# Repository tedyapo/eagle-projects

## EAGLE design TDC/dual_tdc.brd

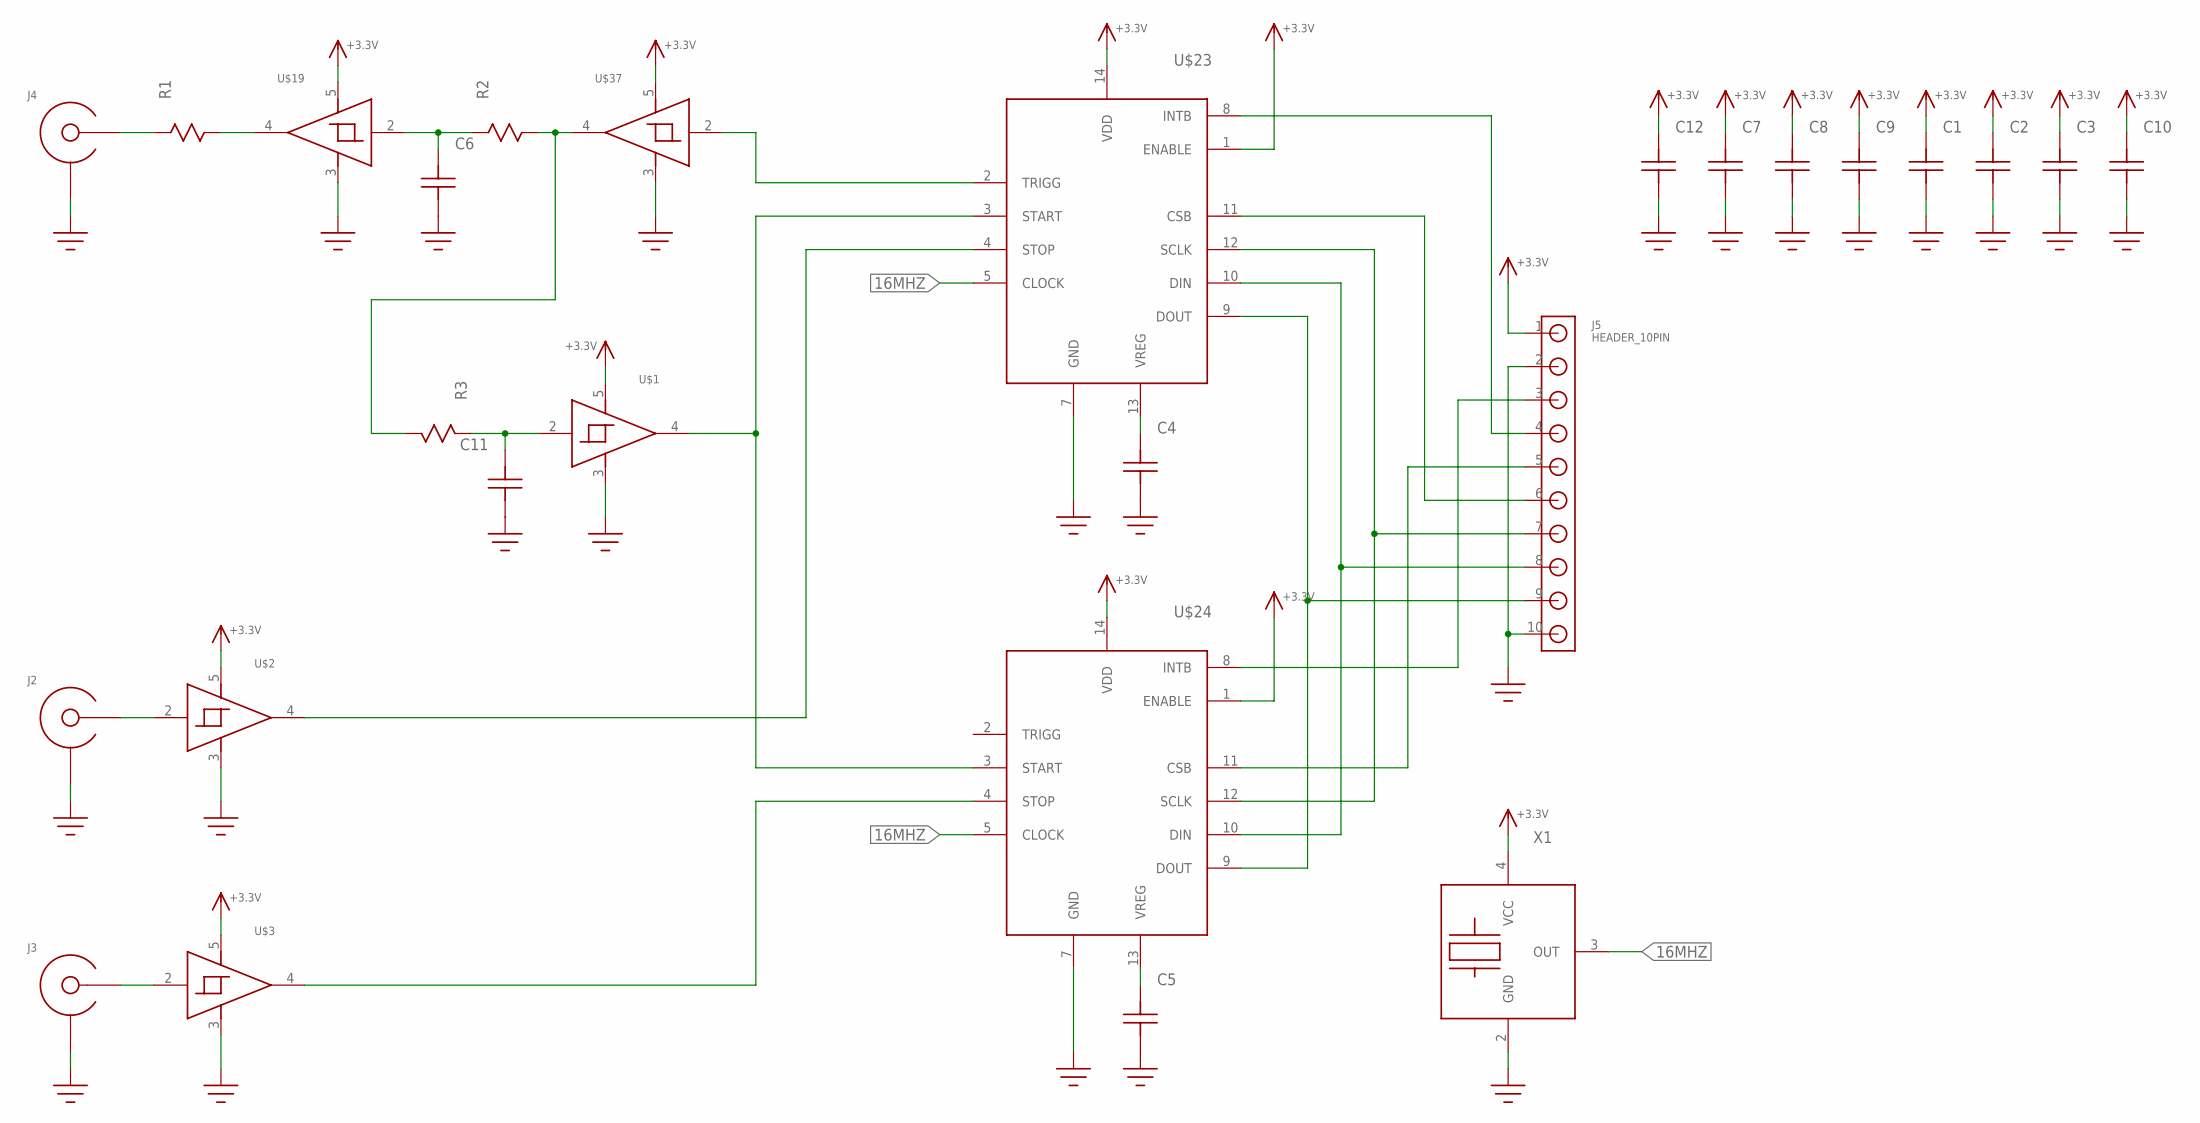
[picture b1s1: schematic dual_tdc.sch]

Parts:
C1, C2, C3, C6, C7, C8, C9, C10, C11, C12: C0603
C4, C5: C0805; 0805
J2, J3, J4: EDGE_LAUNCH_JACK; EDGE_LAUNCH_RF_CON
J5: HEADER_10PIN
R1: R0805
R2, R3: R0603
U$1, U$2, U$3, U$19, U$37: 74LVC1G17; SOT23-5
U$23, U$24: TDC7200TSSOP; TSSOP14
X1: XTAL_OSC; XTAL_3.2X5

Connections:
16MHZ: U$23.5 (CLOCK), U$24.5 (CLOCK), X1.3 (OUT)
+3.3V: C1.P$2, C2.P$2, C3.P$2, C7.P$2, C8.P$2, C9.P$2, C10.P$2, C12.P$2, J5.1, U$1.5 (VCC), U$2.5 (VCC), U$3.5 (VCC), U$19.5 (VCC), U$23.1 (ENABLE), U$23.14 (VDD), U$24.1 (ENABLE), U$24.14 (VDD), U$37.5 (VCC), X1.4 (VCC)
CH1: J2.CENTER, U$2.2 (IN)
CH2: J3.CENTER, U$3.2 (IN)
CSB2: J5.5, U$24.11 (CSB)
DIN: J5.8, U$23.10 (DIN), U$24.10 (DIN)
DOUT: J5.9, U$23.9 (DOUT), U$24.9 (DOUT)
GND: C1.P$1, C2.P$1, C3.P$1, C4.P$1, C5.P$1, C6.P$1, C7.P$1, C8.P$1, C9.P$1, C10.P$1, C11.P$1, C12.P$1, J2.GND@1 (SHIELD), J2.GND@2 (SHIELD), J2.GND@3 (SHIELD), J2.GND@4 (SHIELD), J2.GND@5 (SHIELD), J2.GND@6 (SHIELD), J2.GND@7 (SHIELD), J2.GND@8 (SHIELD), J2.GND@9 (SHIELD), J2.GND@10 (SHIELD), J2.GND@11 (SHIELD), J2.GND@12 (SHIELD), J2.SHIELD@1 (SHIELD), J2.SHIELD@2 (SHIELD), J3.GND@1 (SHIELD), J3.GND@2 (SHIELD), J3.GND@3 (SHIELD), J3.GND@4 (SHIELD), J3.GND@5 (SHIELD), J3.GND@6 (SHIELD), J3.GND@7 (SHIELD), J3.GND@8 (SHIELD), J3.GND@9 (SHIELD), J3.GND@10 (SHIELD), J3.GND@11 (SHIELD), J3.GND@12 (SHIELD), J3.SHIELD@1 (SHIELD), J3.SHIELD@2 (SHIELD), J4.GND@1 (SHIELD), J4.GND@2 (SHIELD), J4.GND@3 (SHIELD), J4.GND@4 (SHIELD), J4.GND@5 (SHIELD), J4.GND@6 (SHIELD), J4.GND@7 (SHIELD), J4.GND@8 (SHIELD), J4.GND@9 (SHIELD), J4.GND@10 (SHIELD), J4.GND@11 (SHIELD), J4.GND@12 (SHIELD), J4.SHIELD@1 (SHIELD), J4.SHIELD@2 (SHIELD), J5.2, J5.10, U$1.3 (GND), U$2.3 (GND), U$3.3 (GND), U$19.3 (GND), U$23.7 (GND), U$24.7 (GND), U$37.3 (GND), X1.2 (GND)
INTB1: J5.4, U$23.8 (INTB)
INTB2: J5.3, U$24.8 (INTB)
unnamed: U$23.2 (TRIGG), U$37.2 (IN)
unnamed: J5.6, U$23.11 (CSB)
unnamed: J4.CENTER, R1.P$1
unnamed: R1.P$2, U$19.4 (OUT)
unnamed: C6.P$2, R2.P$1, U$19.2 (IN)
unnamed: C4.P$2, U$23.13 (VREG)
unnamed: C5.P$2, U$24.13 (VREG)
unnamed: U$1.4 (OUT), U$23.3 (START), U$24.3 (START)
unnamed: C11.P$2, R3.P$1, U$1.2 (IN)
unnamed: U$2.4 (OUT), U$23.4 (STOP)
unnamed: U$3.4 (OUT), U$24.4 (STOP)
unnamed: R2.P$2, R3.P$2, U$37.4 (OUT)
SCLK: J5.7, U$23.12 (SCLK), U$24.12 (SCLK)

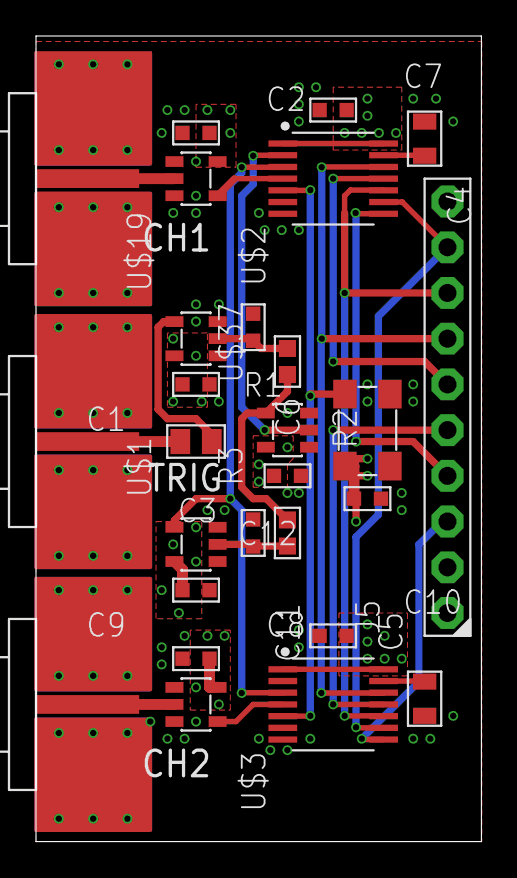
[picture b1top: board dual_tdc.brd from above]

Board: 4 copper layers, 24.7 x 44.8 mm, 27 parts (0 on the bottom side), 23 nets.

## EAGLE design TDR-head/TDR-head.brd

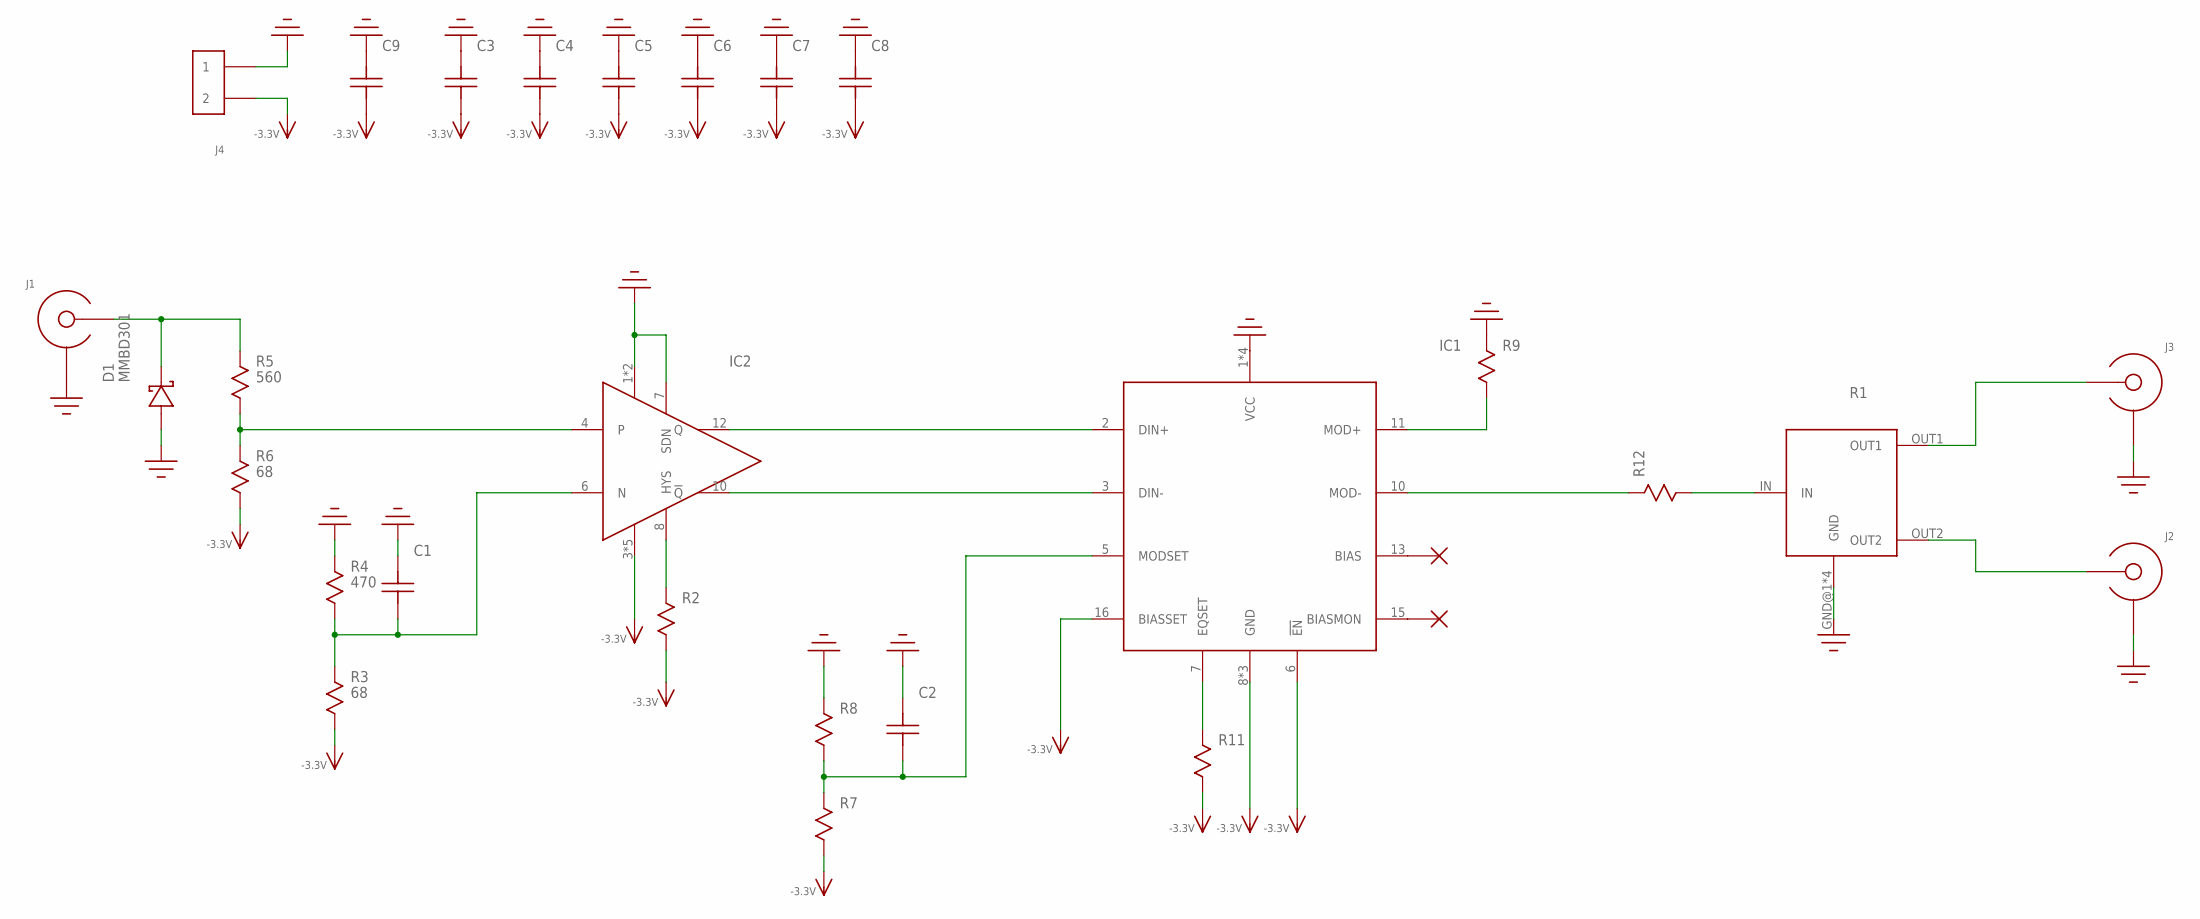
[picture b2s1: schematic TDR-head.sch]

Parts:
C1, C2: C0603
C3, C4, C5, C6, C7, C8: C; C0402
C9: C1206; 1206
D1: MMBD301; SOT-23
IC1: SY88022AL; TQFN16-EP
IC2: ADCMP607; QFN12-3X3
J1, J2, J3: SMA-EDGE-LAUNCH4020N5; SMA_EDGE_LAUNCH_4L_4020_N5
J4: HEADER_2PIN
R1: PS2012G-SPLITTER
R2, R7, R8, R11: R0603
R3, R6: 68; R0603
R4: 470; R0603
R5: 560; R0603
R9, R12: R0402; 0402

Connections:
-3.3V: C3.1, C4.1, C5.1, C6.1, C7.1, C8.1, C9.P$1, IC1.6 (!EN!), IC1.8 (GND), IC1.14 (GND), IC1.16 (BIASSET), IC1.EP (GND), IC2.3 (VEE), IC2.5 (VEE), IC2.9 (VEE), IC2.11 (VEE), IC2.EP (VEE), J4.2, R2.P$2, R3.P$2, R6.P$2, R7.P$2, R11.P$2
GND: C1.P$2, C2.P$2, C3.2, C4.2, C5.2, C6.2, C7.2, C8.2, C9.P$2, D1.1 (ANODE), IC1.1 (VCC), IC1.4 (VCC), IC1.9 (VCC), IC1.12 (VCC), IC2.1 (VCC), IC2.2 (VCC), IC2.7 (SDN), J1.BOTTOM_GND (SHIELD), J1.GND@1 (SHIELD), J1.GND@2 (SHIELD), J1.GND@3 (SHIELD), J1.GND@4 (SHIELD), J1.GND@5 (SHIELD), J1.GND@6 (SHIELD), J1.GND@7 (SHIELD), J1.GND@8 (SHIELD), J1.GND@9 (SHIELD), J1.GND@10 (SHIELD), J1.GND@14 (SHIELD), J1.GND@15 (SHIELD), J1.GND@16 (SHIELD), J1.GND@17 (SHIELD), J1.GND_PAD1 (SHIELD), J1.GND_PAD2 (SHIELD), J1.P$1 (SHIELD), J1.P$2 (SHIELD), J1.P$3 (SHIELD), J1.P$4 (SHIELD), J1.P$5 (SHIELD), J2.BOTTOM_GND (SHIELD), J2.GND@1 (SHIELD), J2.GND@2 (SHIELD), J2.GND@3 (SHIELD), J2.GND@4 (SHIELD), J2.GND@5 (SHIELD), J2.GND@6 (SHIELD), J2.GND@7 (SHIELD), J2.GND@8 (SHIELD), J2.GND@9 (SHIELD), J2.GND@10 (SHIELD), J2.GND@14 (SHIELD), J2.GND@15 (SHIELD), J2.GND@16 (SHIELD), J2.GND@17 (SHIELD), J2.GND_PAD1 (SHIELD), J2.GND_PAD2 (SHIELD), J2.P$1 (SHIELD), J2.P$2 (SHIELD), J2.P$3 (SHIELD), J2.P$4 (SHIELD), J2.P$5 (SHIELD), J3.BOTTOM_GND (SHIELD), J3.GND@1 (SHIELD), J3.GND@2 (SHIELD), J3.GND@3 (SHIELD), J3.GND@4 (SHIELD), J3.GND@5 (SHIELD), J3.GND@6 (SHIELD), J3.GND@7 (SHIELD), J3.GND@8 (SHIELD), J3.GND@9 (SHIELD), J3.GND@10 (SHIELD), J3.GND@14 (SHIELD), J3.GND@15 (SHIELD), J3.GND@16 (SHIELD), J3.GND@17 (SHIELD), J3.GND_PAD1 (SHIELD), J3.GND_PAD2 (SHIELD), J3.P$1 (SHIELD), J3.P$2 (SHIELD), J3.P$3 (SHIELD), J3.P$4 (SHIELD), J3.P$5 (SHIELD), J4.1, R1.GND@1 (GND), R1.GND@2 (GND), R1.GND@3 (GND), R1.GND@4 (GND), R4.P$1, R8.P$1, R9.1
unnamed: J2.CENTER@1 (CENTER), J2.CENTER@2 (CENTER), R1.OUT2
unnamed: J3.CENTER@1 (CENTER), J3.CENTER@2 (CENTER), R1.OUT1
unnamed: IC1.2 (DIN+), IC2.12 (Q)
unnamed: IC1.3 (DIN-), IC2.10 (!Q!)
unnamed: IC2.8 (HYS), R2.P$1
unnamed: C1.P$1, IC2.6 (N), R3.P$1, R4.P$2
unnamed: D1.3 (CATHODE), J1.CENTER@1 (CENTER), J1.CENTER@2 (CENTER), R5.P$1
unnamed: IC2.4, R5.P$2, R6.P$1
unnamed: C2.P$1, IC1.5 (MODSET), R7.P$1, R8.P$2
unnamed: R1.IN, R12.2
unnamed: IC1.11 (MOD+), R9.2
unnamed: IC1.7 (EQSET), R11.P$1
unnamed: IC1.10 (MOD-), R12.1

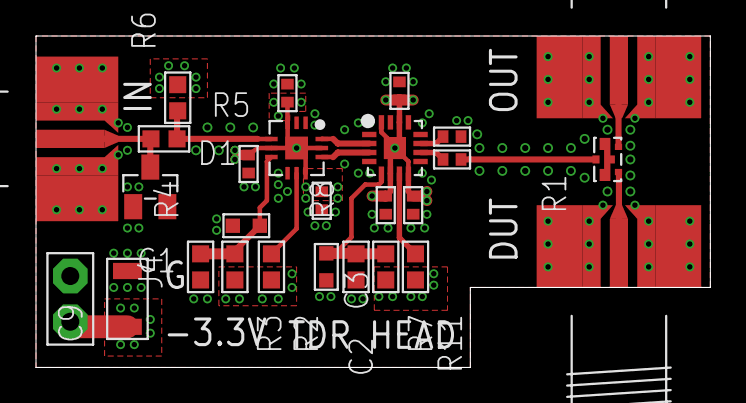
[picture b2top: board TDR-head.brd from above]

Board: 4 copper layers, 37.5 x 18.4 mm, 27 parts (0 on the bottom side), 15 nets.

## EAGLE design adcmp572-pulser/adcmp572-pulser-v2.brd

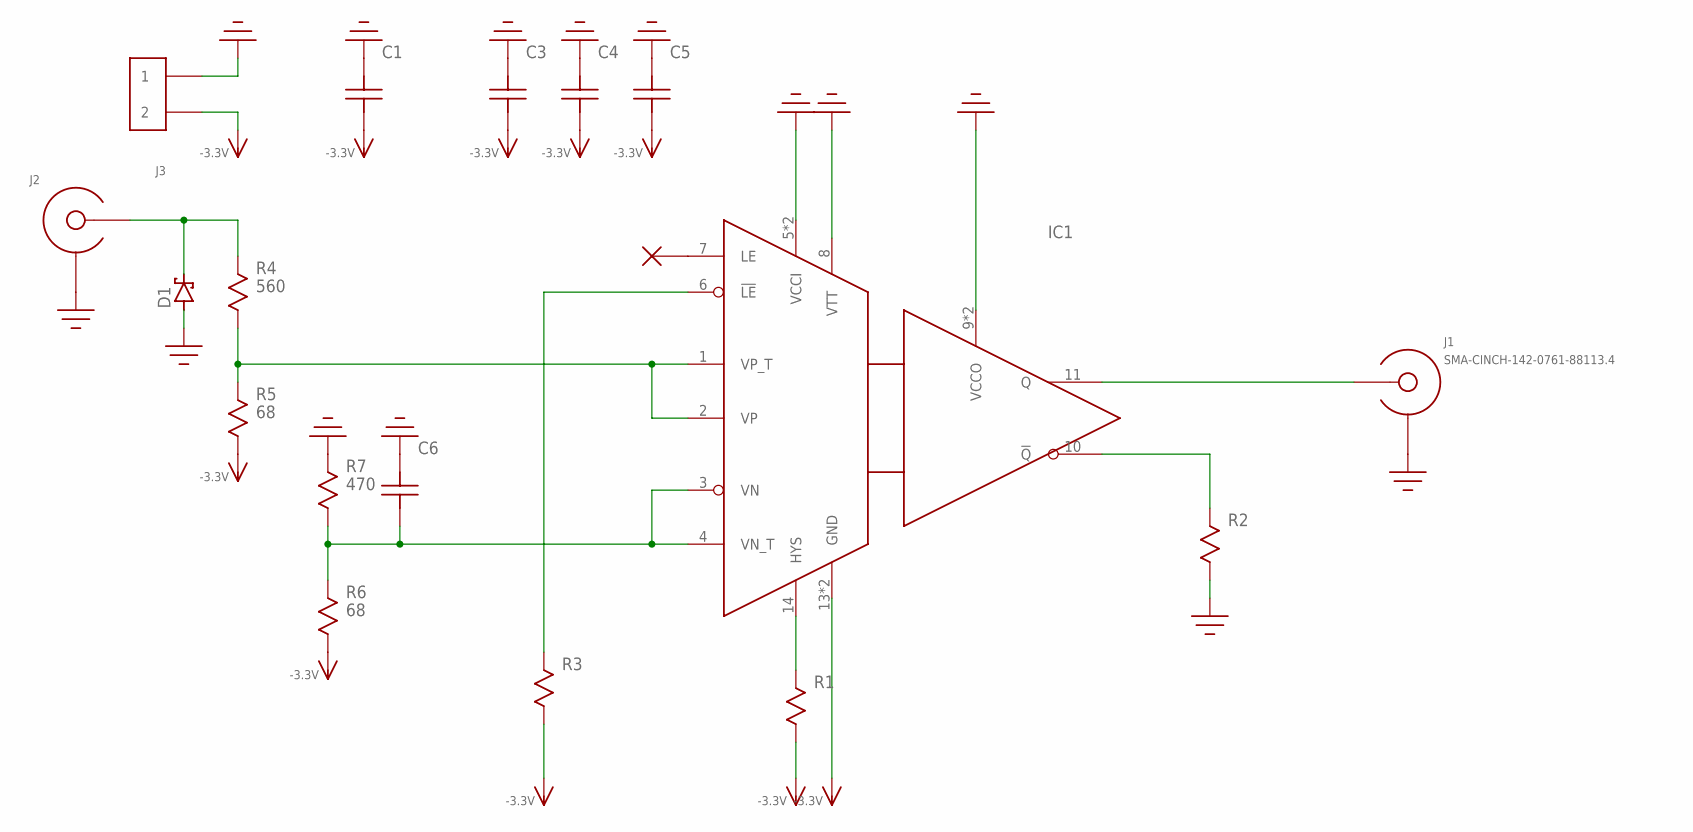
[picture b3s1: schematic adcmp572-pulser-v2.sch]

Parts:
C1: C1206; 1206
C3, C6: C0603
C4, C5: C; C0402
D1: SCHOTTKY; SOT-23
IC1: ADCMP572; TQFN16-EP
J1: SMA-CINCH-142-0761-88113.4; SMA-CINCH-142-0761-881-13.4
J2: SMA-EDGE-LAUNCH4L-4020-TAPER-FIXED; SMA_EDGE_LAUNCH_4L_4020_TAPER_FIXED
J3: HEADER_2PIN
R1, R3: R0603
R2: R0402; 0402
R4: 560; R0603
R5, R6: 68; R0603
R7: 470; R0603

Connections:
-3.3V: C1.P$1, C3.P$1, C4.1, C5.1, IC1.13 (GND), IC1.15 (GND), J3.2, R1.P$2, R3.P$2, R5.P$2, R6.P$2
GND: C1.P$2, C3.P$2, C4.2, C5.2, C6.P$2, D1.1 (A), IC1.5 (VCCI), IC1.8 (VTT), IC1.9 (VCCO), IC1.12 (VCCO), IC1.16 (VCCI), J1.GND@1 (SHIELD), J1.GND@2 (SHIELD), J1.GND@3 (SHIELD), J1.HOLE@1 (SHIELD), J1.HOLE@2 (SHIELD), J1.HOLE@3 (SHIELD), J1.HOLE@4 (SHIELD), J1.VIA@1 (SHIELD), J1.VIA@2 (SHIELD), J1.VIA@3 (SHIELD), J1.VIA@4 (SHIELD), J1.VIA@5 (SHIELD), J1.VIA@6 (SHIELD), J2.BOTTOM_GND (SHIELD), J2.GND@1 (SHIELD), J2.GND@2 (SHIELD), J2.GND@3 (SHIELD), J2.GND@4 (SHIELD), J2.GND@5 (SHIELD), J2.GND@6 (SHIELD), J2.GND@7 (SHIELD), J2.GND@8 (SHIELD), J2.GND@14 (SHIELD), J2.GND@15 (SHIELD), J2.GND@16 (SHIELD), J2.GND@17 (SHIELD), J2.GND_PAD1 (SHIELD), J2.GND_PAD2 (SHIELD), J2.P$1 (SHIELD), J2.P$2 (SHIELD), J3.1, R2.2, R7.P$1
unnamed: IC1.14 (HYS), R1.P$1
unnamed: IC1.10 (!Q!), R2.1
unnamed: C6.P$1, IC1.3 (VN), IC1.4 (VN_T), R6.P$1, R7.P$2
unnamed: IC1.1 (VP_T), IC1.2 (VP), R4.P$2, R5.P$1
unnamed: IC1.6 (!LE!), R3.P$1
unnamed: IC1.11 (Q), J1.CENTER
unnamed: D1.3 (C), J2.CENTER@1 (CENTER), J2.P$3 (CENTER), R4.P$1

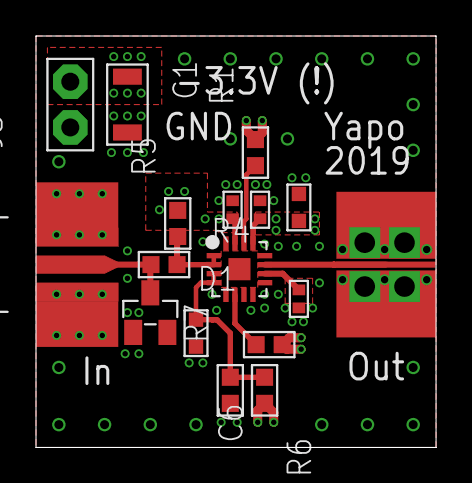
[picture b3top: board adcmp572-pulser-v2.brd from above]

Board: 4 copper layers, 22.2 x 22.9 mm, 17 parts (0 on the bottom side), 9 nets.

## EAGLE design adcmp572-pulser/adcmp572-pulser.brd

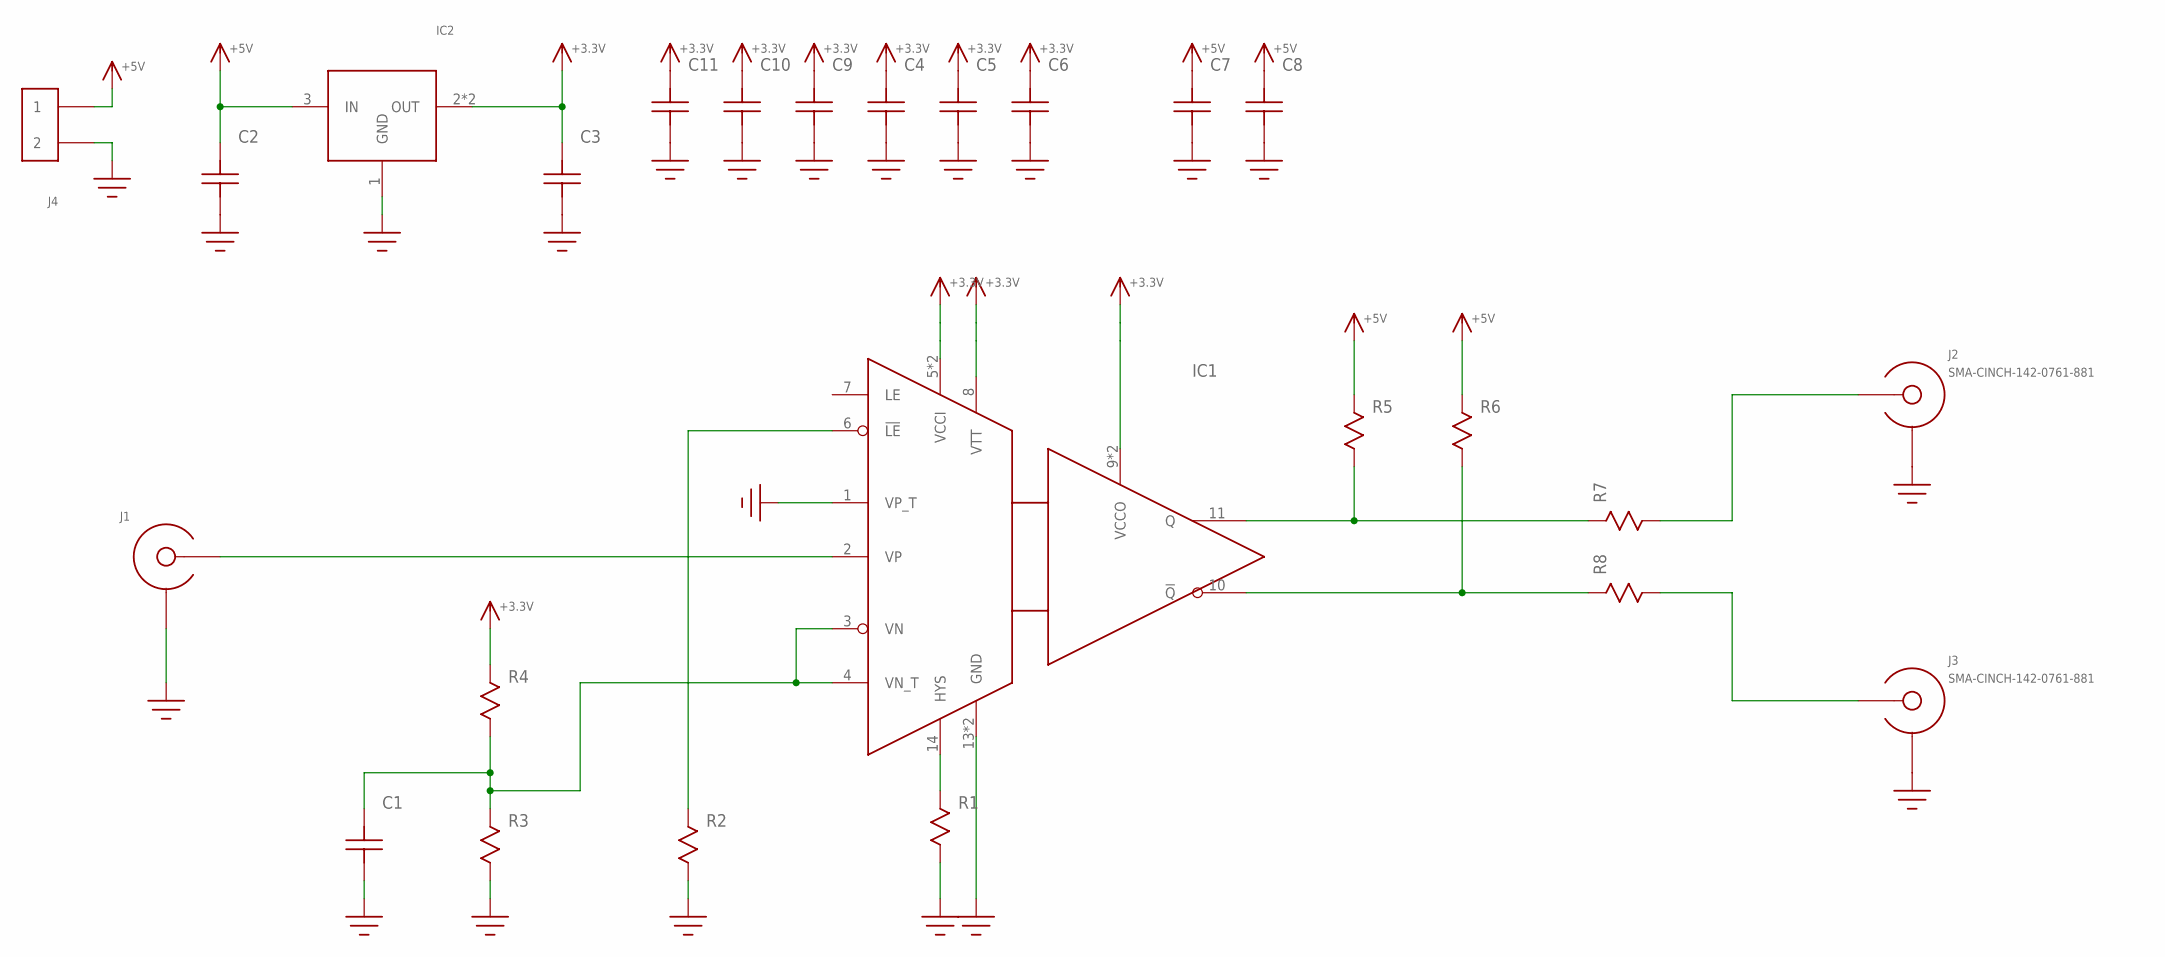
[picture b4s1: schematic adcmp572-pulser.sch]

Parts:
C1: C0603
C2, C3: C1206; 1206
C4, C5, C6, C7, C8, C9: C; C0402
C10, C11: C0201; 0201
IC1: ADCMP572; TQFN16-EP
IC2: AZ1117E; SOT-223
J1: SMA-EDGE-LAUNCH4L-4020-TAPER-FIXED; SMA_EDGE_LAUNCH_4L_4020_TAPER_FIXED
J2, J3: SMA-CINCH-142-0761-881
J4: HEADER_2PIN
R1, R2, R3, R4: R0603
R5, R6, R7, R8: R0402; 0402

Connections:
+3.3V: C3.P$2, C4.2, C5.2, C6.2, C9.2, C10.P$2, C11.P$2, IC1.5 (VCCI), IC1.8 (VTT), IC1.9 (VCCO), IC1.12 (VCCO), IC1.16 (VCCI), IC2.2 (OUT), IC2.4 (OUT), R4.P$1
+5V: C2.P$2, C7.2, C8.2, IC2.3 (IN), J4.1, R5.1, R6.1
GND: C1.P$1, C2.P$1, C3.P$1, C4.1, C5.1, C6.1, C7.1, C8.1, C9.1, C10.P$1, C11.P$1, IC1.1 (VP_T), IC1.13 (GND), IC1.15 (GND), IC2.1 (GND), J1.BOTTOM_GND (SHIELD), J1.GND@1 (SHIELD), J1.GND@2 (SHIELD), J1.GND@3 (SHIELD), J1.GND@4 (SHIELD), J1.GND@5 (SHIELD), J1.GND@6 (SHIELD), J1.GND@7 (SHIELD), J1.GND@8 (SHIELD), J1.GND@14 (SHIELD), J1.GND@15 (SHIELD), J1.GND@16 (SHIELD), J1.GND@17 (SHIELD), J1.GND_PAD1 (SHIELD), J1.GND_PAD2 (SHIELD), J1.P$1 (SHIELD), J1.P$2 (SHIELD), J2.GND@1 (SHIELD), J2.GND@2 (SHIELD), J2.GND@3 (SHIELD), J2.HOLE@1 (SHIELD), J2.HOLE@2 (SHIELD), J2.HOLE@3 (SHIELD), J2.HOLE@4 (SHIELD), J2.VIA@1 (SHIELD), J2.VIA@2 (SHIELD), J2.VIA@3 (SHIELD), J2.VIA@4 (SHIELD), J2.VIA@5 (SHIELD), J2.VIA@6 (SHIELD), J3.GND@1 (SHIELD), J3.GND@2 (SHIELD), J3.GND@3 (SHIELD), J3.HOLE@1 (SHIELD), J3.HOLE@2 (SHIELD), J3.HOLE@3 (SHIELD), J3.HOLE@4 (SHIELD), J3.VIA@1 (SHIELD), J3.VIA@2 (SHIELD), J3.VIA@3 (SHIELD), J3.VIA@4 (SHIELD), J3.VIA@5 (SHIELD), J3.VIA@6 (SHIELD), J4.2, R1.P$2, R2.P$2, R3.P$2
unnamed: IC1.14 (HYS), R1.P$1
unnamed: IC1.6 (!LE!), R2.P$1
unnamed: IC1.2 (VP), J1.CENTER@1 (CENTER), J1.P$3 (CENTER)
unnamed: C1.P$2, IC1.3 (VN), IC1.4 (VN_T), R3.P$1, R4.P$2
unnamed: J2.CENTER, R7.2
unnamed: J3.CENTER, R8.2
unnamed: IC1.11 (Q), R5.2, R7.1
unnamed: IC1.10 (!Q!), R6.2, R8.1

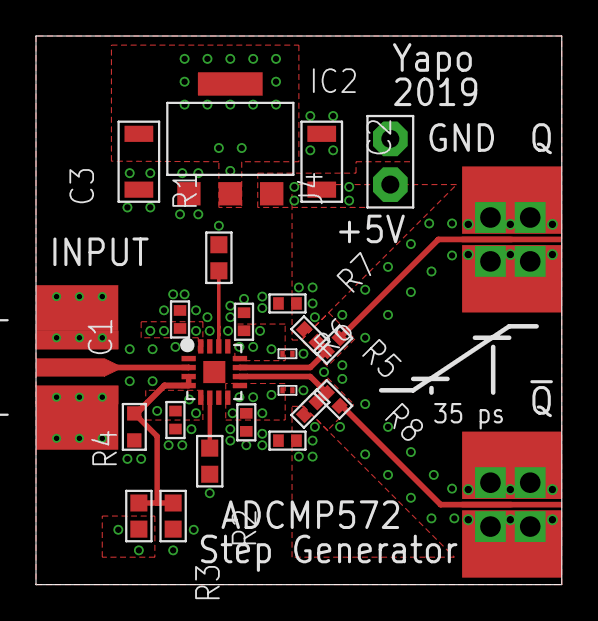
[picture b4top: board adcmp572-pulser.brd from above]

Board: 4 copper layers, 29.2 x 30.5 mm, 25 parts (0 on the bottom side), 11 nets.

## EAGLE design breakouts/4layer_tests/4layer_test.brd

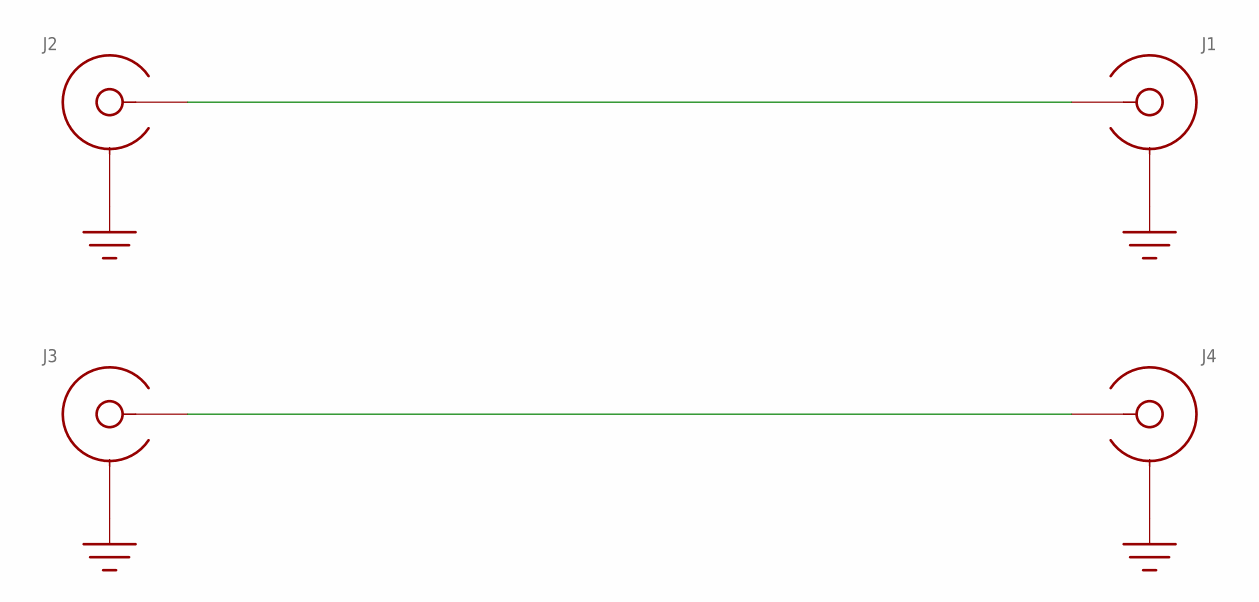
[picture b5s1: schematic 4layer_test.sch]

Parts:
J1, J2, J3, J4: SMA_END_LAUNCH4L; SMA_EDGE_LAUNCH

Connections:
GND: J1.BOTTOM_PAD (SHIELD), J1.GND@1 (SHIELD), J1.GND@2 (SHIELD), J1.GND@3 (SHIELD), J1.GND@4 (SHIELD), J1.GND@5 (SHIELD), J1.GND@6 (SHIELD), J1.GND@7 (SHIELD), J1.GND@8 (SHIELD), J1.GND@14 (SHIELD), J1.GND@15 (SHIELD), J1.GND@16 (SHIELD), J1.GND@17 (SHIELD), J1.GND_PAD1 (SHIELD), J1.GND_PAD2 (SHIELD), J2.BOTTOM_PAD (SHIELD), J2.GND@1 (SHIELD), J2.GND@2 (SHIELD), J2.GND@3 (SHIELD), J2.GND@4 (SHIELD), J2.GND@5 (SHIELD), J2.GND@6 (SHIELD), J2.GND@7 (SHIELD), J2.GND@8 (SHIELD), J2.GND@14 (SHIELD), J2.GND@15 (SHIELD), J2.GND@16 (SHIELD), J2.GND@17 (SHIELD), J2.GND_PAD1 (SHIELD), J2.GND_PAD2 (SHIELD), J3.BOTTOM_PAD (SHIELD), J3.GND@1 (SHIELD), J3.GND@2 (SHIELD), J3.GND@3 (SHIELD), J3.GND@4 (SHIELD), J3.GND@5 (SHIELD), J3.GND@6 (SHIELD), J3.GND@7 (SHIELD), J3.GND@8 (SHIELD), J3.GND@14 (SHIELD), J3.GND@15 (SHIELD), J3.GND@16 (SHIELD), J3.GND@17 (SHIELD), J3.GND_PAD1 (SHIELD), J3.GND_PAD2 (SHIELD), J4.BOTTOM_PAD (SHIELD), J4.GND@1 (SHIELD), J4.GND@2 (SHIELD), J4.GND@3 (SHIELD), J4.GND@4 (SHIELD), J4.GND@5 (SHIELD), J4.GND@6 (SHIELD), J4.GND@7 (SHIELD), J4.GND@8 (SHIELD), J4.GND@14 (SHIELD), J4.GND@15 (SHIELD), J4.GND@16 (SHIELD), J4.GND@17 (SHIELD), J4.GND_PAD1 (SHIELD), J4.GND_PAD2 (SHIELD)
unnamed: J1.CENTER@1 (CENTER), J1.CENTER@2 (CENTER), J2.CENTER@1 (CENTER), J2.CENTER@2 (CENTER)
unnamed: J3.CENTER@1 (CENTER), J3.CENTER@2 (CENTER), J4.CENTER@1 (CENTER), J4.CENTER@2 (CENTER)

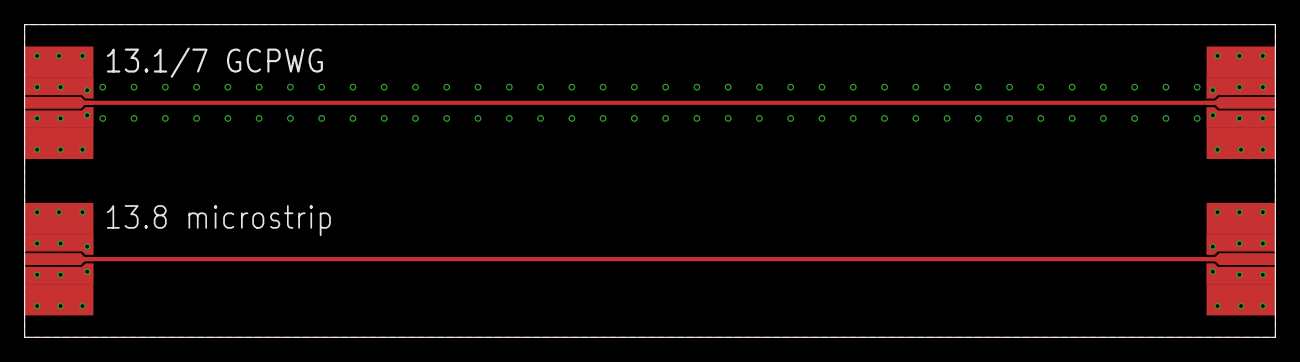
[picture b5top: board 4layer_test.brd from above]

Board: 4 copper layers, 101.6 x 25.4 mm, 4 parts (0 on the bottom side), 3 nets.

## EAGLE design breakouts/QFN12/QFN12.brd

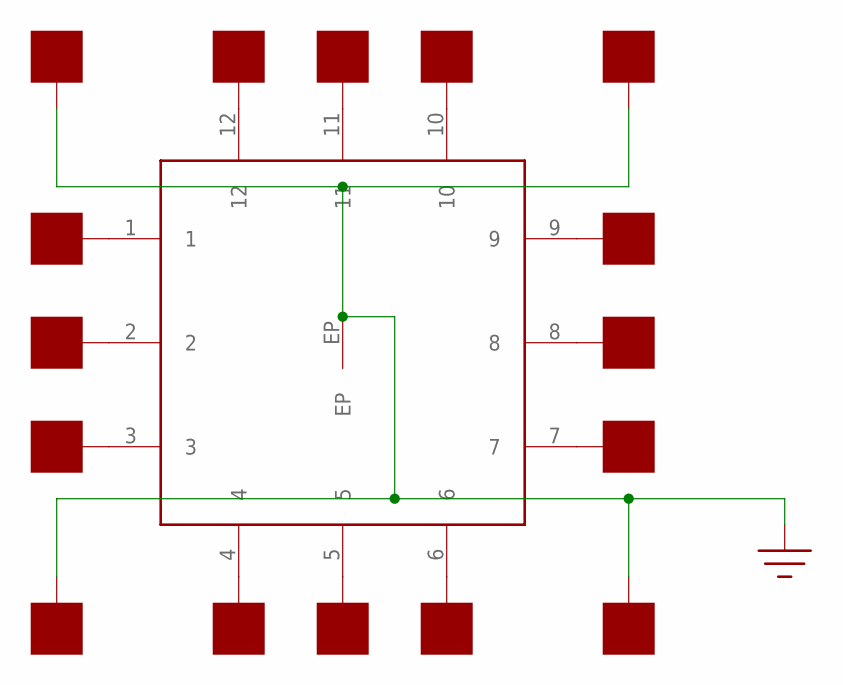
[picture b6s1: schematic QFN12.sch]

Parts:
U$1: QFN12; QFN12-3X3
U$2, U$3, U$4, U$5, U$6, U$7, U$8, U$9, U$10, U$11, U$12, U$13, U$14, U$15, U$16, U$17: PAD50MIL; PAD_50MIL

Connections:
GND: U$1.EP, U$14.P$1, U$15.P$1, U$16.P$1, U$17.P$1
unnamed: U$1.9, U$2.P$1
unnamed: U$1.8, U$3.P$1
unnamed: U$1.7, U$4.P$1
unnamed: U$1.10, U$5.P$1
unnamed: U$1.11, U$6.P$1
unnamed: U$1.12, U$7.P$1
unnamed: U$1.2, U$9.P$1
unnamed: U$1.3, U$10.P$1
unnamed: U$1.4, U$11.P$1
unnamed: U$1.5, U$12.P$1
unnamed: U$1.6, U$13.P$1
unnamed: U$1.1, U$8.P$1

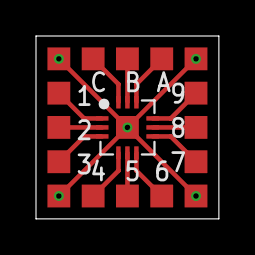
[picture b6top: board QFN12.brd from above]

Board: 2 copper layers, 10.2 x 10.2 mm, 17 parts (0 on the bottom side), 13 nets.
